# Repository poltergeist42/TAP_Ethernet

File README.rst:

================
TAP Raspberry Pi
================

   :Autheur:          `Poltergeist42 <https://github.com/poltergeist42>`_
   :Projet:           TAP Ethernet
   :Licence:          CC BY-NC-SA 4.0
   :Liens:            https://creativecommons.org/licenses/by-nc-sa/4.0/ 

------------------------------------------------------------------------------------------

Description
===========

 Réalisation d'un `TAP Ethernet <https://fr.wikipedia.org/wiki/TAP_r%C3%A9seau.>`_
 
 Ce projet comprend 3 déclinaison :
 
    - L'ensemble complet 
        + Un Raspberry Pi sur lequel est installé Kalli
        + Un TAP 3 ports ethernet (A, B et Monitor)
        + Un Hub USB avec sa propre alimentaion
        + Un adaptateur USB Ethernet
        + Un disque Dur USB
        
    - Le TAP 3 ports (A, B et Monitor) tout seul, pour pouvoir le mettre en place sur un PC
    
    - Le TAP 4 ports (A, B, Monitor Rx et Monitor Tx) plus facille à utiliser dans un
      environement Windows

**N.B** : Ce projet est une déclinaison de cet article : http://www.zem.fr/fabrication-tap-ethernet/

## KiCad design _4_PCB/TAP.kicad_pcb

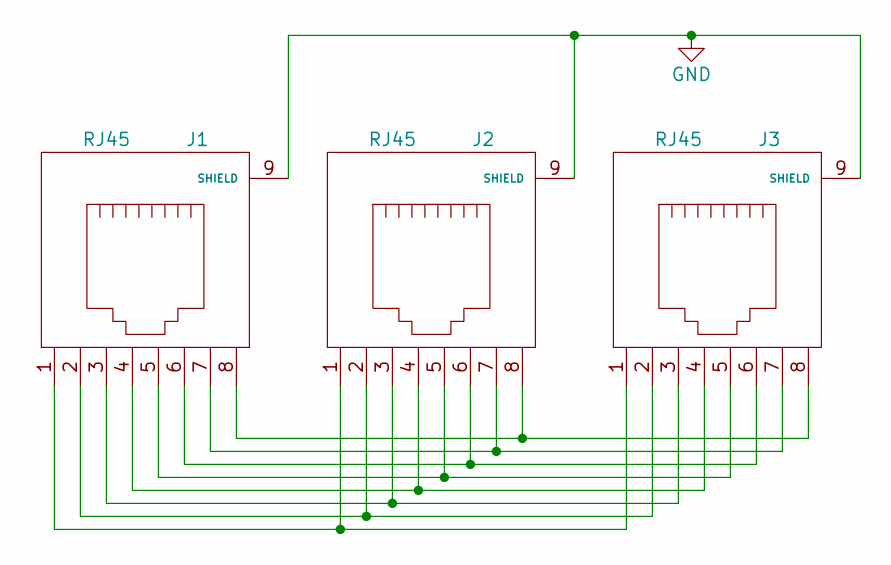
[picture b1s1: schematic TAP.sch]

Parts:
J1, J2, J3: RJ45; RJ45_331-6443

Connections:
GND: J1.9 (SHIELD), J2.9 (SHIELD), J3.9 (SHIELD)
unnamed: J1.1, J2.1, J3.1
unnamed: J1.2, J2.2, J3.2
unnamed: J1.3, J2.3, J3.3
unnamed: J1.4, J2.4, J3.4
unnamed: J1.5, J2.5, J3.5
unnamed: J1.6, J2.6, J3.6
unnamed: J1.7, J2.7, J3.7
unnamed: J1.8, J2.8, J3.8

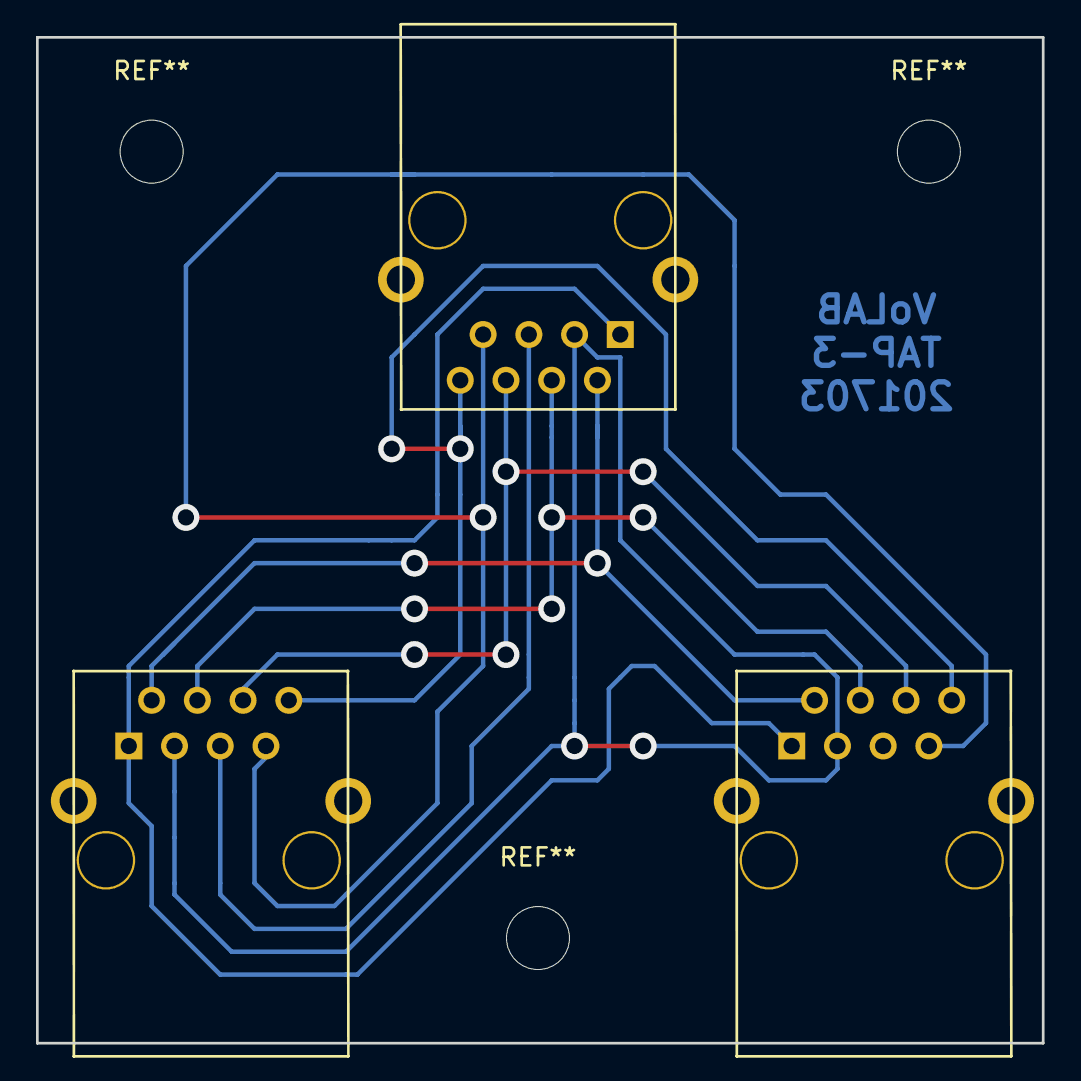
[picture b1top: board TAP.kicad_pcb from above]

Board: 4 copper layers, 55.9 x 55.9 mm, 3 parts (0 on the bottom side), 9 nets.

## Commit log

2017-03-29 Premier commit
2017-03-29 complement sur README.RST
2017-03-29 creation du PCB
2017-04-28 PCB : creation de mask supplementaires (.svg)
